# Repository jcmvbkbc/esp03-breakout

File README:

Programmer & JTAG debugger for ESP8266

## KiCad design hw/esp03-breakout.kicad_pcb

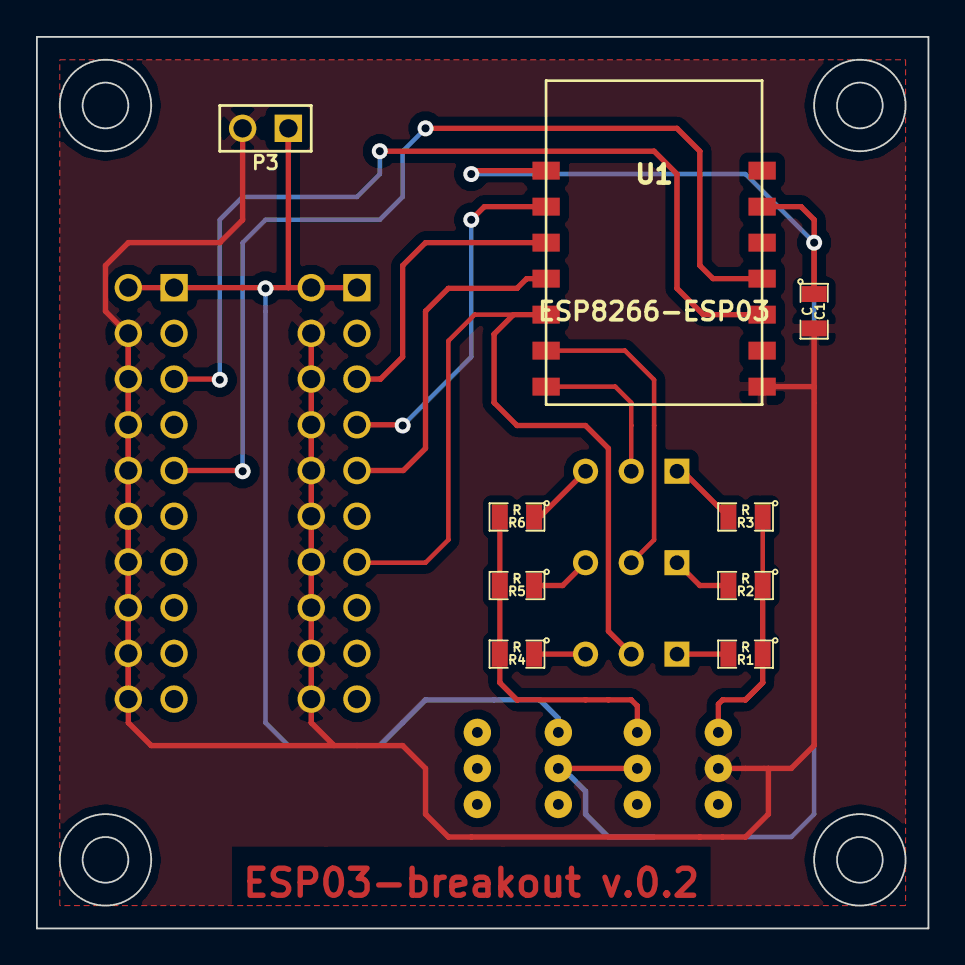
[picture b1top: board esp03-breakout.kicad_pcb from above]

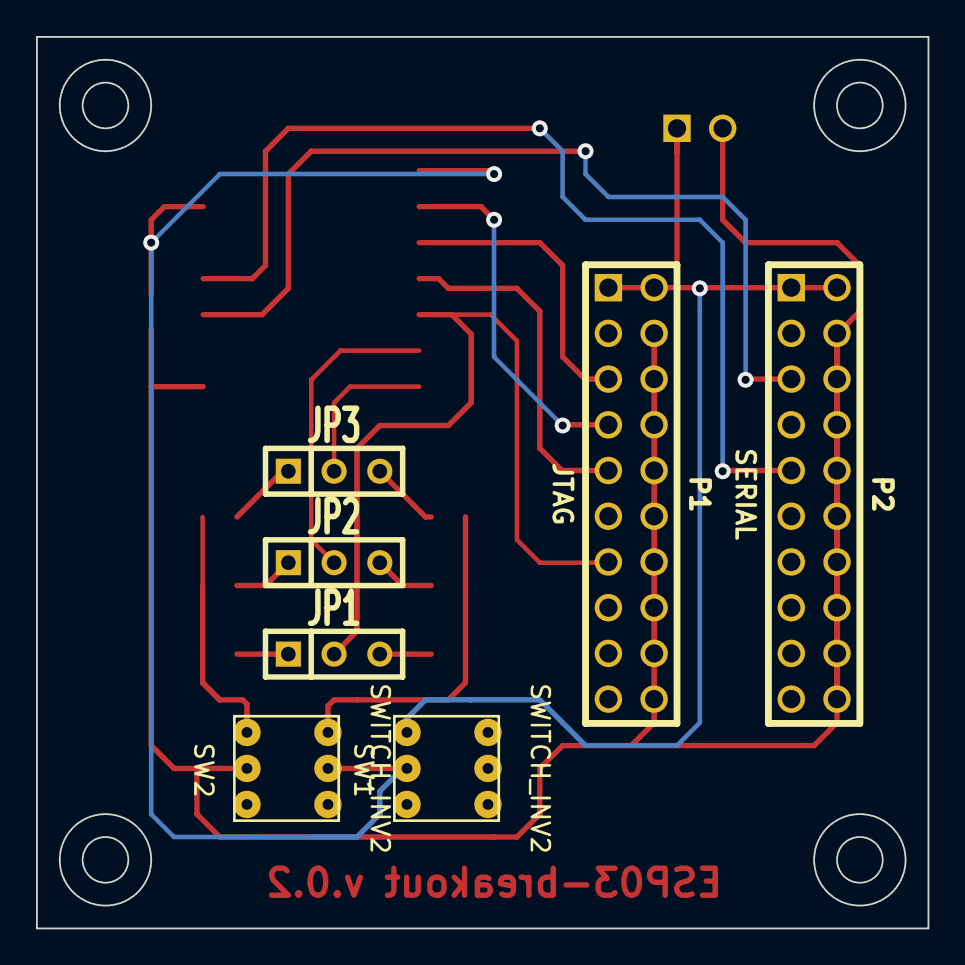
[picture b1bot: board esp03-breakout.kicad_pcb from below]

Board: 2 copper layers, 49.5 x 49.5 mm, 16 parts (7 on the bottom side), 19 nets.

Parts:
C1: C; SM0805
JP1, JP2, JP3: JUMPER3; SIL-3
P1: JTAG; pin_array_10x2
P2: SERIAL; pin_array_10x2
P3: CONN_2; PIN_ARRAY_2X1
R1, R2, R3, R4, R5, R6: R; SM0805
SW1, SW2: SWITCH_INV2
U1: ESP8266-ESP03; esp_03

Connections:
/GPIO0: JP3.2, U1.14
/GPIO2: JP2.2, U1.13
/MTCK: P1.9, U1.11
/MTDI: P1.5, U1.10
/MTDO: JP1.2, P1.13, U1.12
/MTMS: P1.7, U1.9
/RX: P2.5, U1.3
/TX: P2.9, U1.4
GND: C1.2, P1.4, P1.6, P1.8, P1.10, P1.12, P1.14, P1.16, P1.18, P1.20, P2.4, P2.6, P2.8, P2.10, P2.12, P2.14, P2.16, P2.18, P2.20, P3.2, SW2.5, U1.1
unnamed: JP3.1, R3.2
unnamed: JP2.1, R2.2
unnamed: R1.1, R2.1, R3.1, SW2.4
unnamed: R4.2, R5.2, R6.2, SW2.1
unnamed: JP1.1, R1.2
unnamed: JP1.3, R4.1
unnamed: JP2.3, R5.1
unnamed: JP3.3, R6.1
unnamed: C1.1, SW1.5, SW2.2, U1.6, U1.8
VCC: P1.1, P1.2, P2.1, P2.2, P3.1, SW1.4

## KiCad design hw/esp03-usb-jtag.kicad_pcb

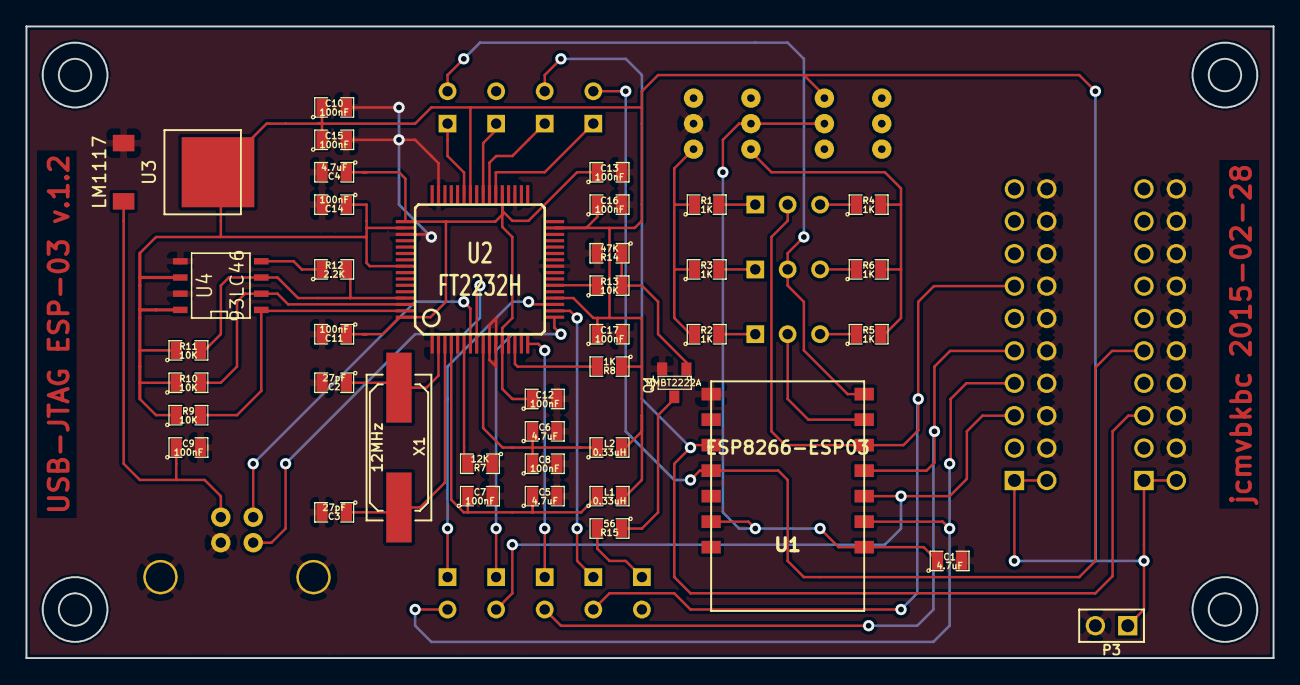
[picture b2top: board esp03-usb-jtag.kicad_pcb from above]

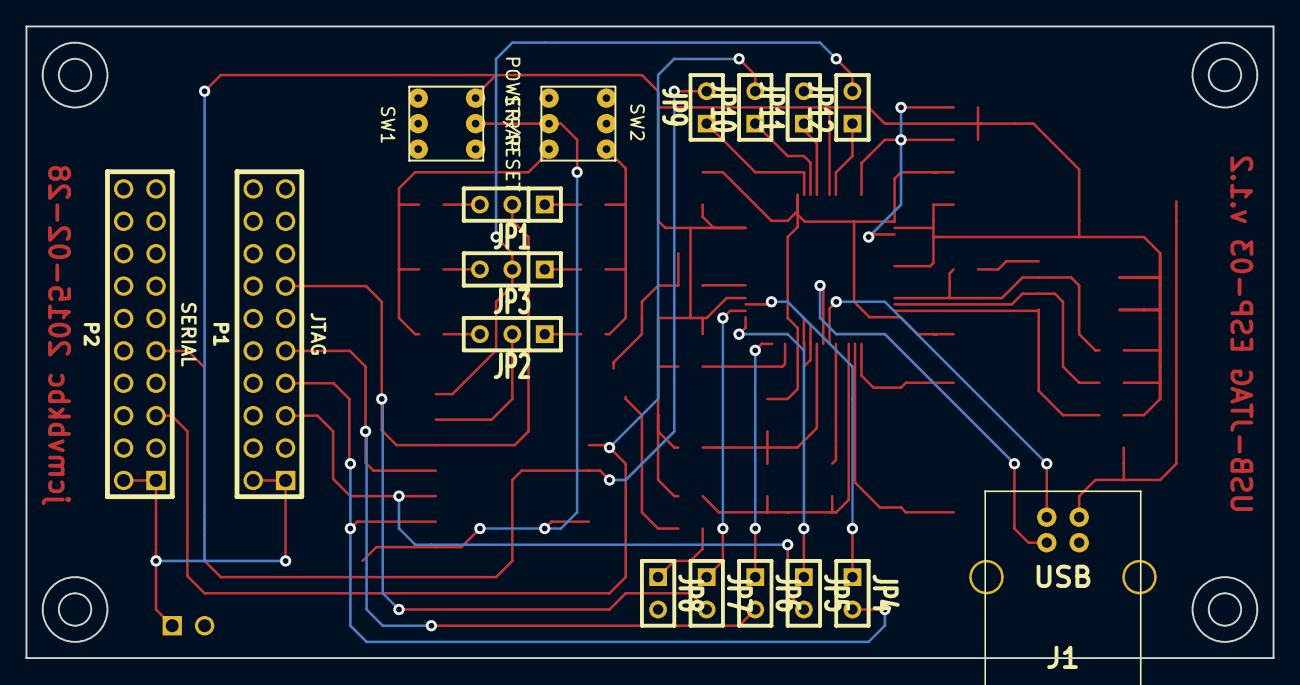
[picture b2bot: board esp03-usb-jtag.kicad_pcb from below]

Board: 2 copper layers, 97.8 x 49.5 mm, 58 parts (17 on the bottom side), 46 nets.

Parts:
C1, C4, C5, C6: 4.7uF; SM0805
C2, C3: 27pF; SM0805
C7, C8, C9, C10, C11, C12, C13, C14, C15, C16, C17: 100nF; SM0805
J1: USB; USB_B
JP1: MTDO; SIL-3
JP2: GPIO2; SIL-3
JP3: GPIO0; SIL-3
JP4, JP5, JP6, JP7, JP8, JP9, JP10, JP11, JP12: JUMPER; SIL-2
L1, L2: 0.33uH; SM0805
P1: JTAG; pin_array_10x2
P2: SERIAL; pin_array_10x2
P3: CONN_2; PIN_ARRAY_2X1
Q1: MMBT2222A; SOT23
R1, R2, R3, R4, R5, R6, R8: 1K; SM0805
R7: 12K; SM0805
R9, R10, R11, R13: 10K; SM0805
R12: 2.2K; SM0805
R14: 47K; SM0805
R15: 56; SM0805
SW1: POWER/RESET; SWITCH_INV2
SW2: STRAP; SWITCH_INV2
U1: ESP8266-ESP03; esp_03
U2: FT2232H; VQFP64
U3: LM1117; TO252
U4: 93LC46; SO8N
X1: 12MHz; Q_49U3HMS

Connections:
+1.8V: C4.1, C11.1, C12.1, C13.1, U2.12, U2.37, U2.49, U2.64
+3.3V: C10.1, C14.1, C15.1, C16.1, C17.1, L1.2, L2.2, P1.1, P1.2, P2.1, P2.2, P3.1, R8.1, R9.1, R10.1, R11.1, SW1.1, U2.20, U2.31, U2.42, U2.50, U2.56, U3.VO, U4.6, U4.8
/FT_DTR: JP12.1, U2.43
/FT_MTCK: JP6.1, U2.16
/FT_MTDI: JP5.1, U2.17
/FT_MTDO: JP7.1, U2.18
/FT_MTMS: JP4.1, U2.19
/FT_RTS: JP11.1, U2.40
/FT_RXD: JP10.1, U2.39
/FT_SRST: R13.1, U2.22
/FT_TXD: JP9.1, U2.38
/GPIO0: JP3.2, JP12.2, U1.14
/GPIO2: JP2.2, U1.13
/MTCK: JP6.2, P1.9, U1.11
/MTDI: JP5.2, P1.5, U1.10
/MTDO: JP1.2, JP7.2, P1.13, U1.12
/MTMS: JP4.2, P1.7, U1.9
/RESET: JP8.2, JP11.2
/RX: JP10.2, P2.5, U1.3
/SRST: JP8.1, R15.2
/TX: JP9.2, P2.9, U1.4
GND: C1.2, C2.2, C3.2, C4.2, C5.2, C6.2, C7.2, C8.2, C9.2, C10.2, C11.2, C12.2, C13.2, C14.2, C15.2, C16.2, C17.2, J1.4, J1.5, J1.6, P1.4, P1.6, P1.8, P1.10, P1.12, P1.14, P1.16, P1.18, P1.20, P2.4, P2.6, P2.8, P2.10, P2.12, P2.14, P2.16, P2.18, P2.20, P3.2, Q1.2, R7.1, R14.2, SW2.5, U1.1, U2.1, U2.5, U2.10, U2.11, U2.13, U2.15, U2.25, U2.35, U2.47, U2.51, U3.GND, U4.5, U4.7
unnamed: R9.2, U2.63, U4.1
unnamed: R10.2, U2.62, U4.2
unnamed: R11.2, R12.2, U2.61, U4.3
unnamed: R12.1, U4.4
unnamed: J1.2, U2.7
unnamed: C9.1, J1.1, U3.VI
unnamed: C3.1, U2.3, X1.2
unnamed: C6.1, C8.1, L2.1, U2.9
unnamed: C5.1, C7.1, L1.1, U2.4
unnamed: J1.3, U2.8
unnamed: R7.2, U2.6
unnamed: R8.2, U2.14
unnamed: Q1.1, R13.2, R14.1
unnamed: Q1.3, R15.1
unnamed: C2.1, U2.2, X1.1
unnamed: R4.2, R5.2, R6.2, SW2.1
unnamed: JP3.1, R3.2
unnamed: JP1.1, R1.2
unnamed: JP1.3, R4.1
unnamed: JP2.1, R2.2
unnamed: JP2.3, R5.1
unnamed: JP3.3, R6.1
unnamed: R1.1, R2.1, R3.1, SW2.4
unnamed: C1.1, SW1.2, SW2.2, U1.6, U1.8

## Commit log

2015-02-14 initial
2015-02-14 hw: add initial board version
2015-02-21 hw: add FT2232H symbol to library
2015-02-21 hw: add 93LC46 chip to library
2015-02-21 hw: add LM1117 chip to library
2015-02-23 hw: add TO252 footprint to mod
2015-02-23 hw: basic breakout board update
2015-02-23 hw: add usb-jtag schematics and board
2015-02-23 hw/drawings: add usb-jtag board drawings
2015-02-24 hw: add JTAG and UART connections to FT chip
2015-02-24 hw: update PCB with FTDI JTAG and UART
2015-02-24 hw/drawings: update drawings with FTDI JTAG and UART
2015-02-26 hw: usb-jtag: update JTAG and UART connectors location
2015-02-28 hw: add NPN_KEY to library
2015-02-28 hw: invert the SRST signal, add it to PCB, update drawings
2015-03-05 hw/esp03-breakout: shrink the board, fix bugs, update drawings
    Flip connectors, jumpers and buttons to the back side.
